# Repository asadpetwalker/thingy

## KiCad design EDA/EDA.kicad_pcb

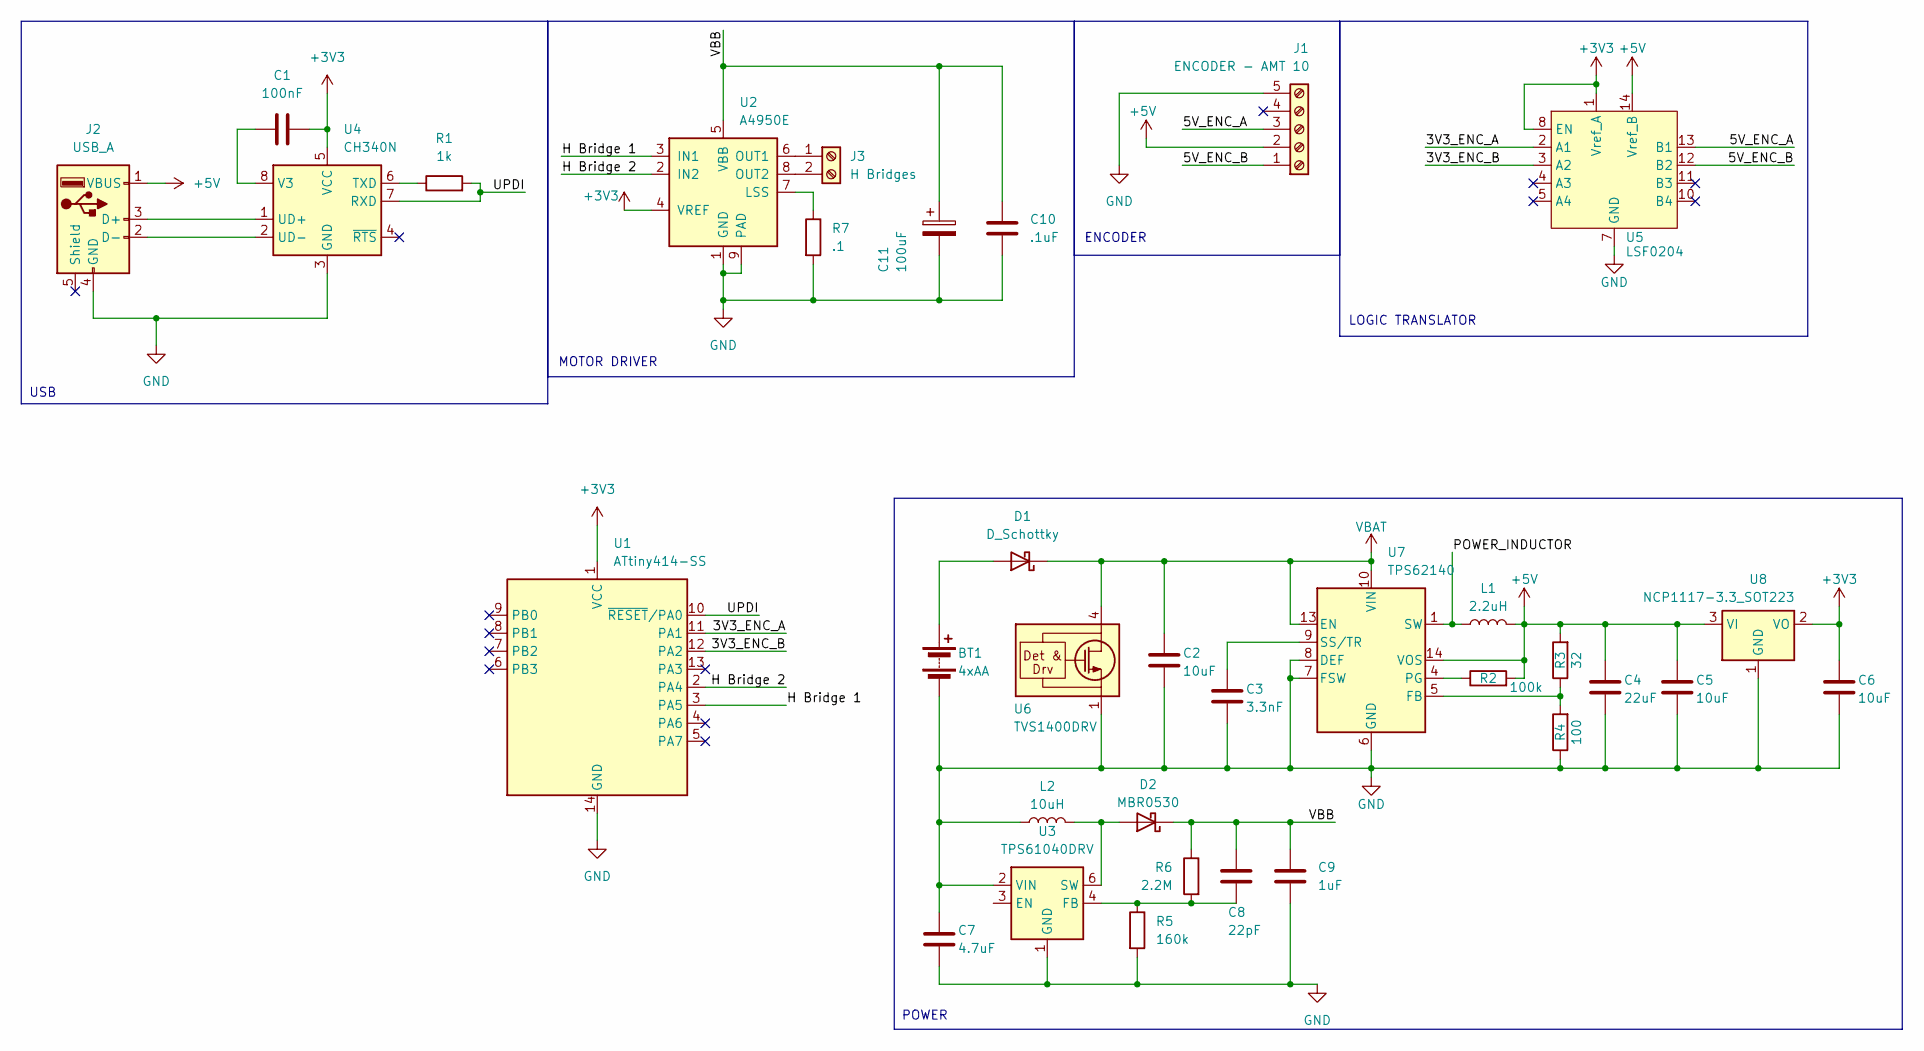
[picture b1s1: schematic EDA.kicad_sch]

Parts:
BT1: 4xAA; TerminalBlock_Phoenix_PT-1,5-2-5.0-H_1x02_P5.00mm_Horizontal
C1: 100nF; C_0603_1608Metric
C2, C5, C6: 10uF; C_0805_2012Metric
C3: 3.3nF; C_0603_1608Metric
C4: 22uF; C_0805_2012Metric
C7: 4.7uF; C_0603_1608Metric
C8: 22pF; C_0603_1608Metric
C9: 1uF; C_0603_1608Metric
C10: .1uF; C_0603_1608Metric
C11: 100uF; C_0603_1608Metric
D1: D_Schottky; TO-277A
D2: MBR0530; D_SOD-123
J1: ENCODER - AMT 10; TerminalBlock_Phoenix_PT-1,5-5-5.0-H_1x05_P5.00mm_Horizontal
J2: USB_A; USB3_A_Molex_48393-001
J3: H Bridges; TerminalBlock_Phoenix_PT-1,5-2-5.0-H_1x02_P5.00mm_Horizontal
L1: 2.2uH; L_Vishay_IHLP-1212
L2: 10uH; L_Vishay_IHLP-1212
R1: 1k; R_0603_1608Metric
R2: 100k; R_0603_1608Metric
R3: 32; R_0603_1608Metric
R4: 100; R_0603_1608Metric
R5: 160k; R_0603_1608Metric
R6: 2.2M; R_0603_1608Metric
R7: .1; R_0603_1608Metric
U1: ATtiny414-SS; SOIC-14_3.9x8.7mm_P1.27mm
U2: A4950E; SOIC-8-1EP_3.9x4.9mm_P1.27mm_EP2.41x3.3mm
U3: TPS61040DRV; WSON-6-1EP_2x2mm_P0.65mm_EP1x1.6mm
U4: CH340N; SOP-8_3.9x4.9mm_P1.27mm
U5: LSF0204; Texas_S-PVQFN-N14
U6: TVS1400DRV; WSON-6-1EP_2x2mm_P0.65mm_EP1x1.6mm_ThermalVias
U7: TPS62140; VQFN-16-1EP_3x3mm_P0.5mm_EP1.68x1.68mm_ThermalVias
U8: NCP1117-3.3_SOT223; SOT-223-3_TabPin2

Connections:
+3V3: C1.1, C6.1, U1.1 (VCC), U2.4 (VREF), U4.5 (VCC), U5.1 (Vref_A), U5.8 (EN), U8.2 (VO)
+5V: C4.1, C5.1, J1.2, J2.1 (VBUS), L1.2, R2.2, R3.2, U5.14 (Vref_B), U7.14 (VOS), U8.3 (VI)
/3V3_ENC_A: U1.11 (PA1), U5.2 (A1)
/3V3_ENC_B: U1.12 (PA2), U5.3 (A2)
/5V_ENC_A: J1.3, U5.13 (B1)
/5V_ENC_B: J1.1, U5.12 (B2)
/H Bridge 1: U1.3 (PA5), U2.3 (IN1)
/H Bridge 2: U1.2 (PA4), U2.2 (IN2)
/POWER_INDUCTOR: L1.1, U7.1 (SW), U7.2 (SW), U7.3 (SW)
/UPDI: R1.2, U1.10 (~RESET/PA0), U4.7 (RXD)
/VBB: C8.1, C9.1, C10.1, C11.1, D2.1 (K), R6.1, U2.5 (VBB)
GND: BT1.2 (-), C2.2, C3.2, C4.2, C5.2, C6.2, C7.1, C7.2, C9.2, C10.2, C11.2, J1.5, J2.4 (GND), L2.1, R4.1, R5.2, R7.2, U1.14 (GND), U2.1 (GND), U2.9 (PAD), U3.1 (GND), U3.2 (VIN), U4.3 (GND), U5.7 (GND), U6.1 (GND), U6.2 (GND), U6.3 (GND), U6.7 (GND), U7.6 (GND), U7.7 (FSW), U7.8 (DEF), U7.15 (GND), U7.16 (GND), U7.17 (GND), U8.1 (GND)
unnamed: BT1.1 (+), D1.2 (A)
unnamed: D2.2 (A), L2.2, U3.6 (SW)
unnamed: J2.3 (D+), U4.1 (UD+)
unnamed: J2.2 (D-), U4.2 (UD-)
unnamed: J3.1, U2.6 (OUT1)
unnamed: J3.2, U2.8 (OUT2)
unnamed: R7.1, U2.7 (LSS)
unnamed: C8.2, R5.1, R6.2, U3.4 (FB)
unnamed: R1.1, U4.6 (TXD)
unnamed: C1.2, U4.8 (V3)
unnamed: R3.1, R4.2, U7.5 (FB)
unnamed: R2.1, U7.4 (PG)
unnamed: C3.1, U7.9 (SS/TR)
VBAT: C2.1, D1.1 (K), U6.4 (IN), U6.5 (IN), U6.6 (IN), U7.10 (VIN), U7.11 (VIN), U7.12 (VIN), U7.13 (EN)

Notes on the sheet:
POWER
LOGIC TRANSLATOR
USB
ENCODER
MOTOR DRIVER

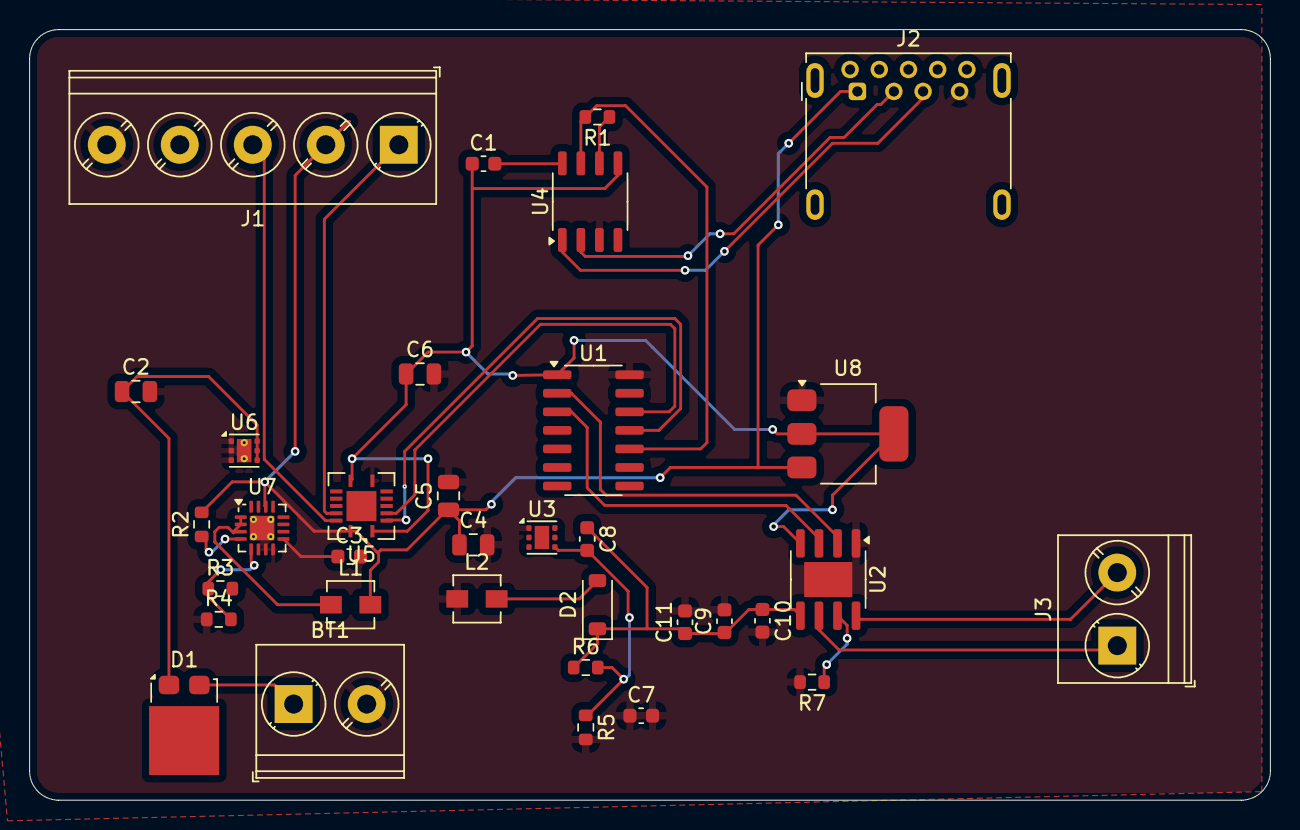
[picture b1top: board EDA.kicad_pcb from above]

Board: 2 copper layers, 85.0 x 52.8 mm, 34 parts (0 on the bottom side), 26 nets.

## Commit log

2025-06-08 zone
